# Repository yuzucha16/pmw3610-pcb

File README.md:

# PMW3610 PCB

[PixArt PMW3610DM-SUDU](https://www.pixart.com/products-detail/21/PMW3610DM-SUDU) low power laser mouse sensor breakout board.

- Base on schematic from [siderakb/pmw3610-pcb](https://github.com/siderakb/pmw3610-pcb).
- Be operated with 3.3V voltage level ONLY.
- Outlined as narrow as possible for side mount horizontally and perpendicular on low profile keyboards.

*Figure 1: Size comparing to Seeed XIAO BLE*

## PCB

Online preview avaliable [here](https://kicanvas.org/?github=https%3A%2F%2Fgithub.com%2Fbadjeff%2Fpmw3610-pcb), powered by [KiCanvas](https://github.com/theacodes/kicanvas).

*Figure 2: PCB edgecuts dimension*

### BOM

|Ref|Value|Footprint|
|-|-|-|
|C1|3.3uF/16V|SMD 0603|
|C2, C3|100nF|SMD 0603|
|C4|100nF X7R|SMD 0603|
|C5|10nF|SMD 0603|
|C6|10uF X7R|SMD 0603|
|C7|10nF X7R|SMD 0603|
|C8, C9|1uF|SMD 0603|
|C10| DNI |SMD 0603|
|R1|10k|SMD 0603|
|U1|PMW3610|16 Pin|
|U2|TLV74318|SOT-23-5|
|J1, J2|2.54mm Pin header||
- DNI: don't install.
- SMD 0603 (Imperial) aka 1608 Metric.
- PMW3610 needs to be used with LM18-LSI lens.
- `R1` is optional/additional RESET pull up resistor, RESET pin of PMW3610 has a built in weak pull up circuit.
- `U2` LDO can be replace by RT9193-18GB, change `C10` to 22nF.
- Solder extra decoupling capacitors (C4, C6, C7) directly to the pins of the sensor, if needed.

### Board Characteristics

- Copper layer count: 2
- Board thickness: 1.6 mm
- Board overall dimensions: 15.5 x 30 mm

### Voltage level config

- 3.3V logic
- VIN: 3.3V

## License

Available under the [CERN-OHL-P v2](/LICENSE) permissive license.

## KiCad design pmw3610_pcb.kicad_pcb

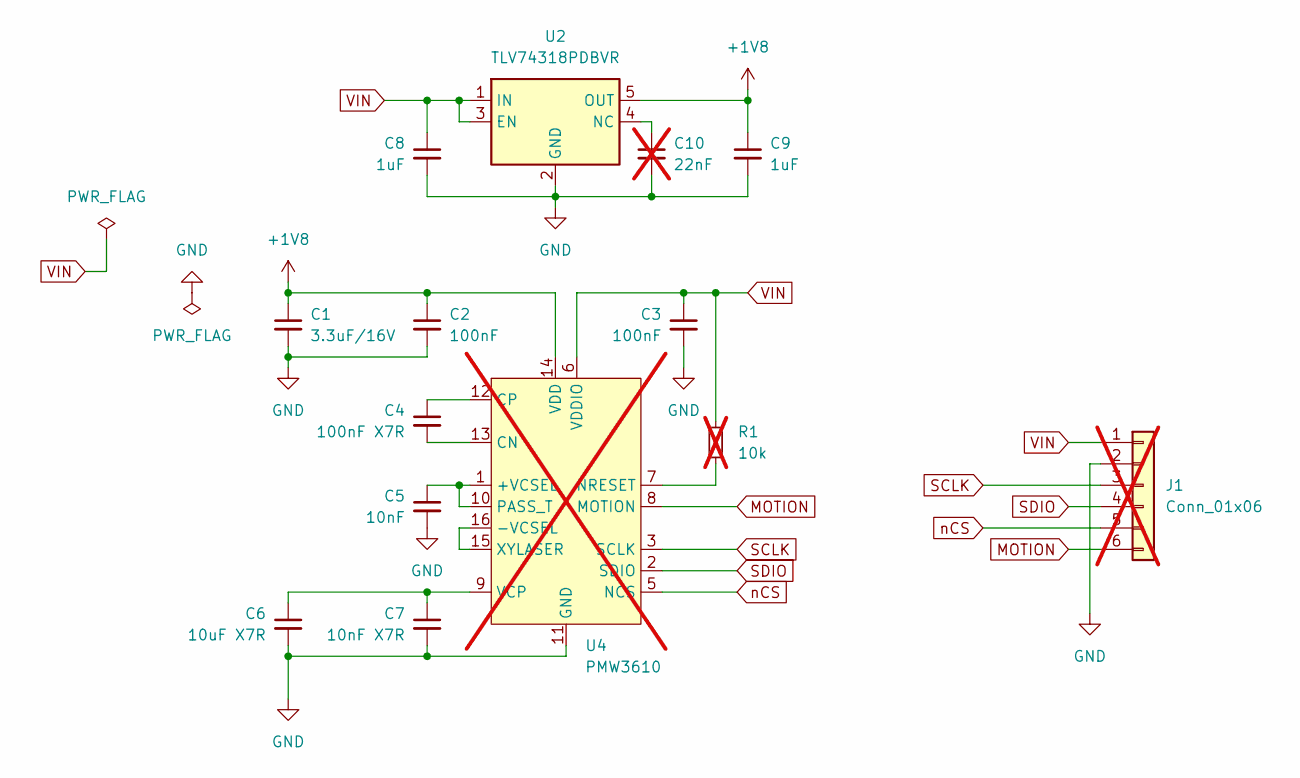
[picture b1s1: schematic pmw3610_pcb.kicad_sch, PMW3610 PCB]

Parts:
C1: 3.3uF/16V; C_0603_1608Metric
C2, C3: 100nF; C_0603_1608Metric
C4: 100nF X7R; C_0603_1608Metric
C5: 10nF; C_0603_1608Metric
C6: 10uF X7R; C_0603_1608Metric
C7: 10nF X7R; C_0603_1608Metric
C8, C9: 1uF; C_0603_1608Metric
C10: 22nF; C_0603_1608Metric; not fitted
J1: Conn_01x06; PinHeader_1x06_P2.54mm_Vertical; not fitted
R1: 10k; R_0603_1608Metric; not fitted
U2: TLV74318PDBVR; SOT-23-5_HandSoldering
U4: PMW3610; PMW3610DM-SUDU 16Pin; not fitted

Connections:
+1V8: C1.1, C2.1, C9.1, U2.5 (OUT), U4.14 (VDD)
GND: C1.2, C2.2, C3.2, C5.2, C6.2, C7.2, C8.2, C9.2, C10.2, J1.2, U2.2 (GND), U4.11 (GND)
MOTION: J1.6, U4.8 (MOTION)
unnamed: C10.1, U2.4 (NC)
unnamed: C5.1, U4.1 (+VCSEL), U4.10 (PASS_T)
unnamed: U4.15 (XYLASER), U4.16 (-VCSEL)
unnamed: C4.2, U4.13 (CN)
unnamed: C4.1, U4.12 (CP)
unnamed: R1.2, U4.7 (NRESET)
unnamed: C6.1, C7.1, U4.9 (VCP)
SCLK: J1.3, U4.3 (SCLK)
SDIO: J1.4, U4.2 (SDIO)
VIN: C3.1, C8.1, J1.1, R1.1, U2.1 (IN), U2.3 (EN), U4.6 (VDDIO)
nCS: J1.5, U4.5 (NCS)

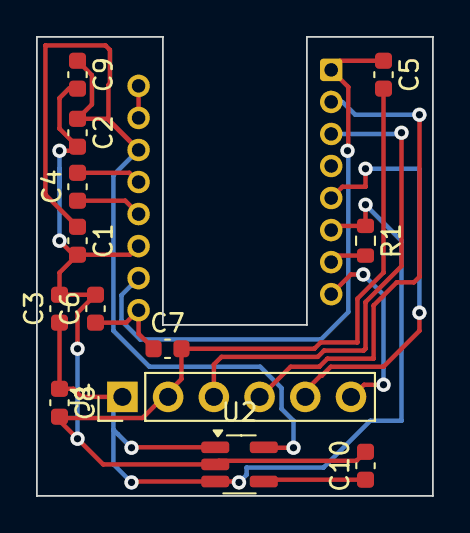
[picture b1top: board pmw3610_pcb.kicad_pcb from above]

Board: 2 copper layers, 22.0 x 25.5 mm, 14 parts (1 on the bottom side), 14 nets.

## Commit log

2024-10-01 init commit
2024-10-01 fix KiCanvas url
2024-12-14 modify size (25mm x 22mm)
2024-12-14 [jlcpcb] Add order files
2024-12-15 [V0] for jlcpcb

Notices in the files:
pmw3610_pcb.kicad_pcb:
Open Source Hardware, CERN-OHL-P v2
